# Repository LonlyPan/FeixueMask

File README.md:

# 飞雪面具控制板源码

- **[English](/README_EN.md)**

飞雪面具控制板是[飞雪面具](https://www.bilibili.com/video/BV1Dy4y1i72c)的配套产品。

## 如何找到文件

### 00_Priority README
该目录下存放了该控制板项目的全部**技术文档**，对该项目的程序源码、PCB设计都有详细说明，请首先阅读。
>文档目前尚未编写完成
>
### 01_Firmware
该目录下存放了 **软件/程序** 相关的全部源文件

### 02_Electronics
该目录下存放了 **电路/PCB** 相关的全部源文件

### 04_others
即不属于 软件/程序 也不属于 电路/PCB，但和本项目相关的其它文件

###  README.txt
每个文件夹下都有该文档，请**首先阅读**。这包含有其所处文件夹的阅读索引及一些重要说明。

## FeixueMask 1.0
FeixueMask 1.0 是该固件的初始版本，已经经过测试，可正常使用。

在[发布页面](https://github.com/LonlyPan/FeixueMask/releases)下载早期版本的FeixueMask固件。
>目前还未发布任何历史版本

## 支持

为了获得最佳的配置和故障排除帮助，请使用以下资源：
- 哔哩哔哩：[猩造](https://space.bilibili.com/16614468/)  
- 聊天催更Q群：779627778

## 许可协议

FeixueMask 是遵循 [GPL license](/LICENSE) 协议发行的，因为我们相信开放式开发。 GPL附带了权利和义务。 无论您使用 FeixueMask 固件作为开源产品还是封闭源产品的驱动程序，都必须保持 FeixueMask 开放，并且必须根据要求向最终用户提供兼容的 FeixueMask 源代码。 遵守 FeixueMask 许可证的最直接方法是在 Github 上制作 FeixueMask 的分支，执行您的修改，并将用户引导到您修改后的分支。

虽然我们不能禁止在具有封闭源代码或有专利保护的产品中使用此代码，但我们还是希望您选择其他固件，或者最好自己制作。

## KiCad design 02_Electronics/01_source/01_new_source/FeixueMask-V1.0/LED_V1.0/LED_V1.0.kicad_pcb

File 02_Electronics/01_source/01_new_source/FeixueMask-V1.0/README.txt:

LED_V1.0 -------------------------------- LED灯板设计源文件
main_V1.0 ------------------------------- 主控板设计源文件
最终输出文件 ----------------------------- BOM、Gerber、原理图pdf

A1.0  2020-08-18
  原理图错误：
    1. Q1 引脚1、2颠倒（main、LED）
    2. RX接MCU引脚错误，应接PA10（main）
    3. 电容C2~5 值错误，应为 0.1uF（main）

V1.0  2020-08-21
   版本更新：
     1. 修复上一版设计错误（main、LED）
     2. LED灯板重新设计，三色灯改为单色灯（LED）
  版本错误：

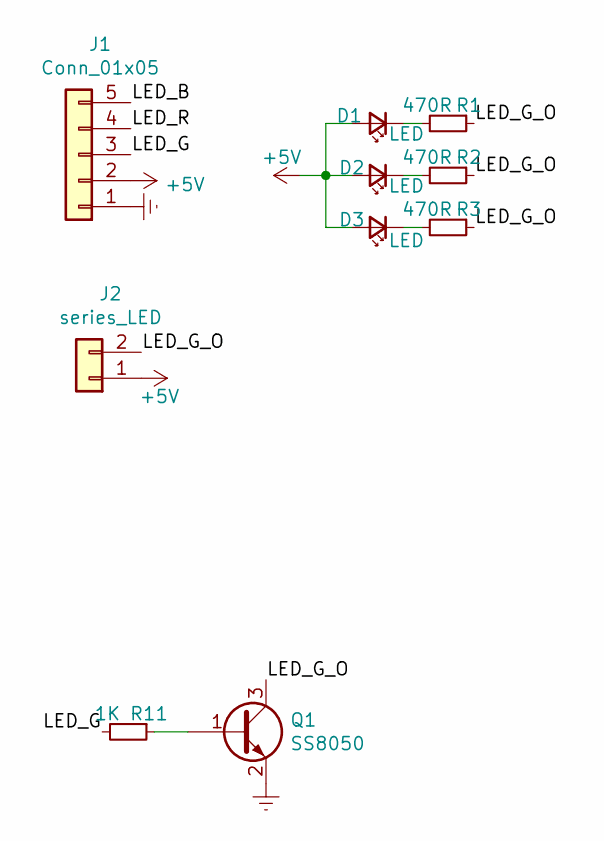
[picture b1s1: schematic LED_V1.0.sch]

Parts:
D1, D2, D3: LED; LED_0805_2012Metric
J1: Conn_01x05; FPC-0.7x5-Handsoldering
J2: series_LED; Pad-2.2mm_1.5x1.5
Q1: SS8050; SOT-23
R1, R2, R3: 470R; R_0603_1608Metric
R11: 1K; R_0603_1608Metric

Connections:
+5V: D1.2 (A), D2.2 (A), D3.2 (A), J1.2, J2.1
/LED_B: J1.5
/LED_G: J1.3, R11.2
/LED_G_O: J2.2, Q1.3 (C), R1.1, R2.1, R3.1
/LED_R: J1.4
Earth: J1.1, Q1.2 (E)
unnamed: D1.1 (K), R1.2
unnamed: D2.1 (K), R2.2
unnamed: D3.1 (K), R3.2
unnamed: Q1.1 (B), R11.1

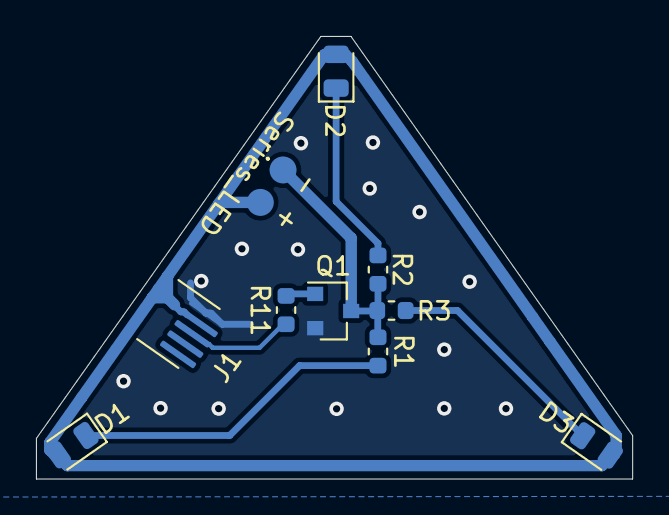
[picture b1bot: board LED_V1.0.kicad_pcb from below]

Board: 2 copper layers, 33.1 x 24.6 mm, 10 parts (10 on the bottom side), 8 nets.

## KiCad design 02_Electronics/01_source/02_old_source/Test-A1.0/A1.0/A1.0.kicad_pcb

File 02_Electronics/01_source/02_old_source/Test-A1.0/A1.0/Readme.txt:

R2 R3标注颠倒
STM32 RX引脚错误，PA8改为PA10

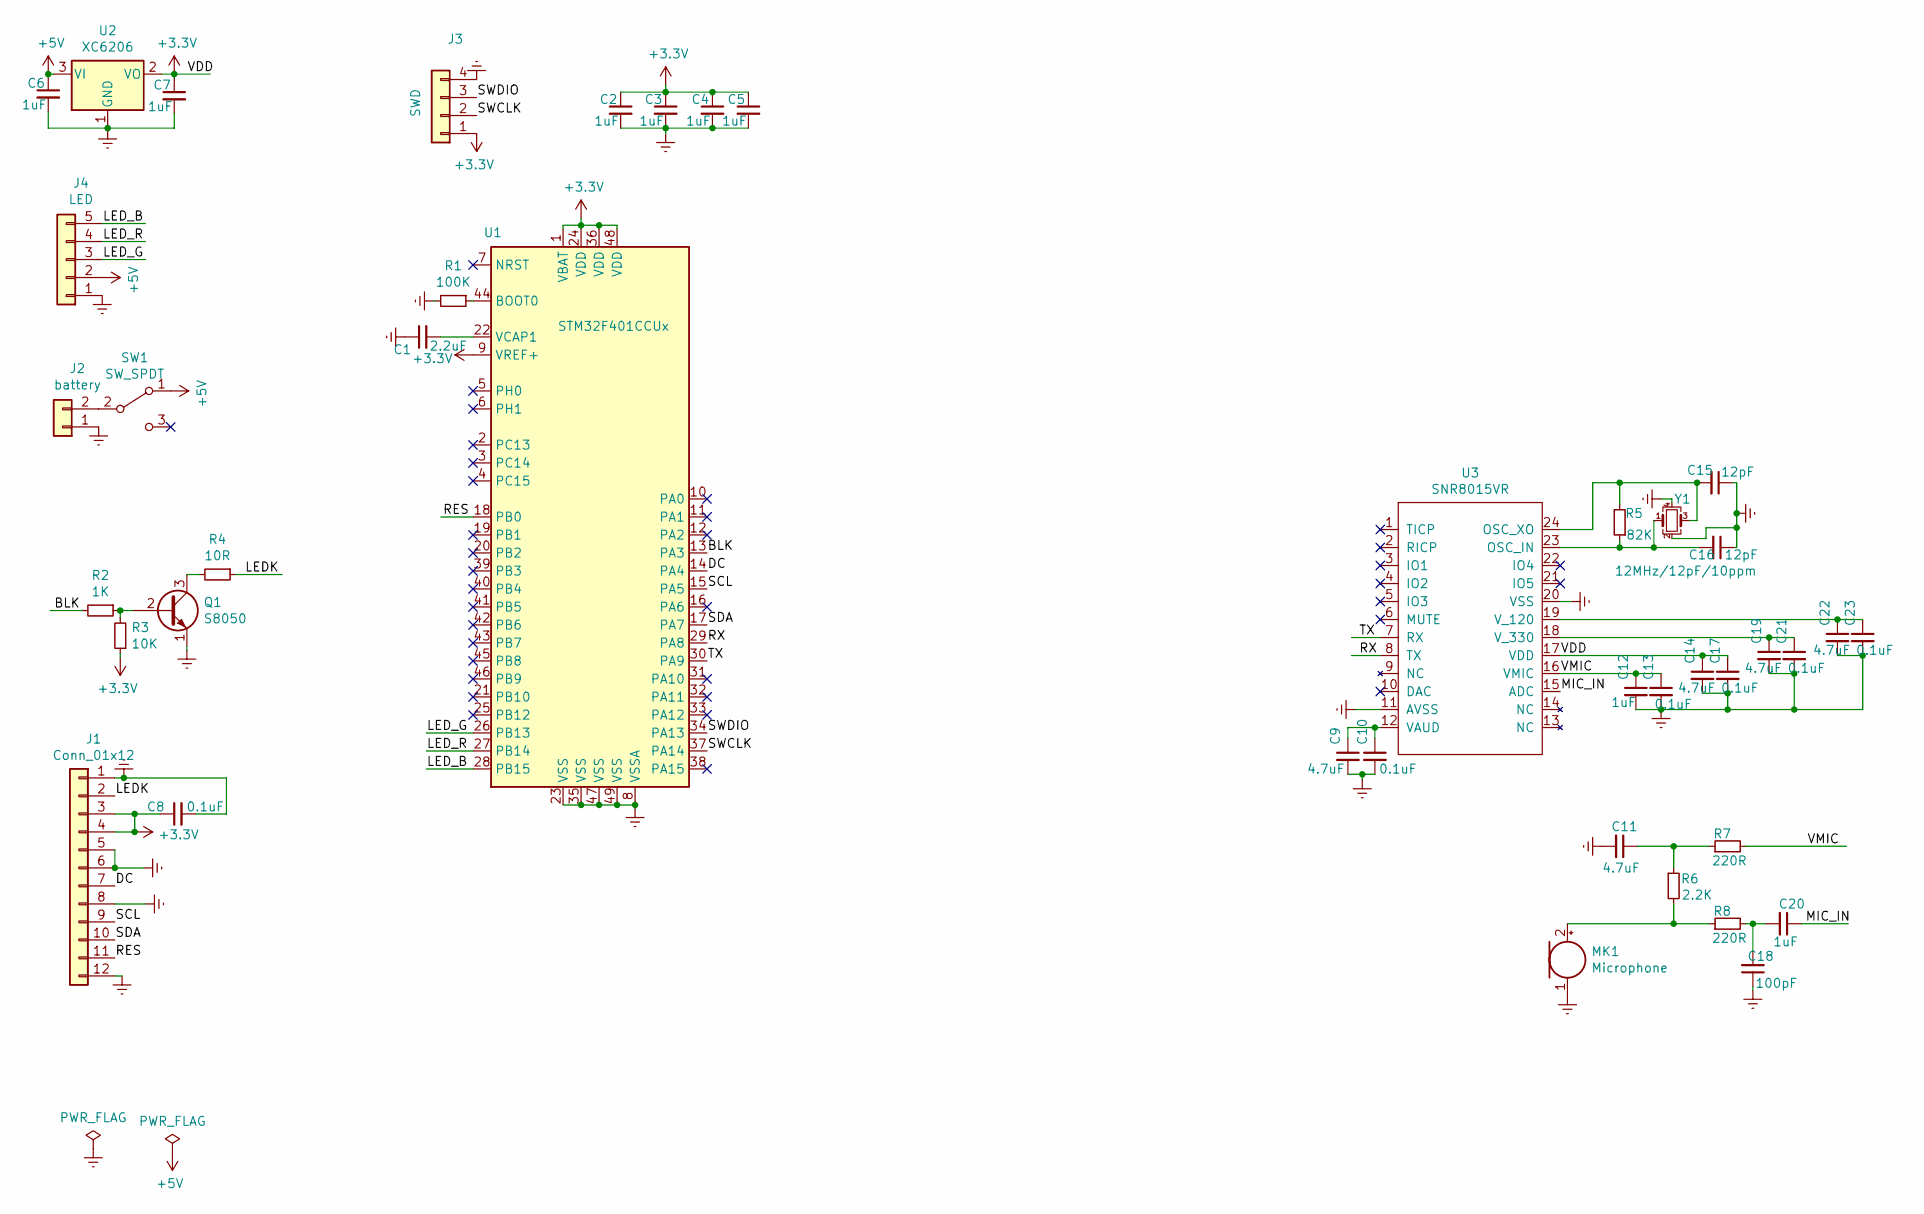
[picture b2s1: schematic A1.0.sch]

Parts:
C1: 2.2uF; C_0603_1608Metric
C2, C3, C4, C5, C6, C7, C12, C20: 1uF; C_0603_1608Metric
C8, C10, C13, C17, C21, C23: 0.1uF; C_0603_1608Metric
C9, C11, C14, C19, C22: 4.7uF; C_0603_1608Metric
C15, C16: 12pF; C_0603_1608Metric
C18: 100pF; C_0603_1608Metric
J1: Conn_01x12; FPC-0.7-Handsoldering-1.28-TFT
J2: battery; Speaker
J3: SWD; Con-1x4-P1.25mm
J4: LED; FPC-0.7x5-Handsoldering
MK1: Microphone; Condenser-Microphone-4012
Q1: S8050; SOT-23
R1: 100K; R_0603_1608Metric
R2: 1K; R_0603_1608Metric
R3: 10K; R_0603_1608Metric
R4: 10R; R_0603_1608Metric
R5: 82K; R_0603_1608Metric
R6: 2.2K; R_0603_1608Metric
R7, R8: 220R; R_0603_1608Metric
SW1: SW_SPDT; MSKT-12C00-switch-smd
U1: STM32F401CCUx; QFN-48-1EP_7x7mm_P0.5mm_EP5.6x5.6mm
U2: XC6206; SOT-23
U3: SNR8015VR; QSOP-24_3.9x8.7mm_P0.635mm
Y1: 12MHz/12pF/10ppm; Crystal_SMD_2520-4Pin_2.5x2.0mm

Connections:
+3V3: C2.1, C3.1, C4.1, C5.1, C7.1, C8.1, C14.1, C17.1, J1.3, J1.4, J3.1, R3.1, U1.1 (VBAT), U1.9 (VREF+), U1.24 (VDD), U1.36 (VDD), U1.48 (VDD), U2.2 (VO), U3.17 (VDD)
+5V: C6.1, J4.2, SW1.1 (A), U2.3 (VI)
/BLK: R2.2, U1.13 (PA3)
/DC: J1.7, U1.14 (PA4)
/LEDK: J1.2, R4.1
/LED_B: J4.5, U1.28 (PB15)
/LED_G: J4.3, U1.26 (PB13)
/LED_R: J4.4, U1.27 (PB14)
/MIC_IN: C20.1, U3.15 (ADC)
/RES: J1.11, U1.18 (PB0)
/RX: U1.29 (PA8), U3.8 (TX)
/SCL: J1.9, U1.15 (PA5)
/SDA: J1.10, U1.17 (PA7)
/SWCLK: J3.2, U1.37 (PA14)
/SWDIO: J3.3, U1.34 (PA13)
/TX: U1.30 (PA9), U3.7 (RX)
/VMIC: C12.1, C13.1, R7.2, U3.16 (VMIC)
Earth: C1.1, C2.2, C3.2, C4.2, C5.2, C6.2, C7.2, C8.2, C9.2, C10.2, C11.2, C12.2, C13.2, C14.2, C15.1, C16.1, C17.2, C18.1, C19.2, C21.2, C22.2, C23.2, J1.1, J1.5, J1.6, J1.8, J1.12, J2.1, J3.4, J4.1, MK1.1 (-), Q1.1 (E), R1.2, U1.8 (VSSA), U1.23 (VSS), U1.35 (VSS), U1.47 (VSS), U1.49 (VSS), U2.1 (GND), U3.11 (AVSS), U3.20 (VSS), Y1.2, Y1.4
unnamed: C1.2, U1.22 (VCAP1)
unnamed: C9.1, C10.1, U3.12 (VAUD)
unnamed: C11.1, R6.1, R7.1
unnamed: C15.2, R5.2, U3.24 (OSC_XO), Y1.3
unnamed: C16.2, R5.1, U3.23 (OSC_IN), Y1.1
unnamed: C18.2, C20.2, R8.2
unnamed: C19.1, C21.1, U3.18 (V_330)
unnamed: C22.1, C23.1, U3.19 (V_120)
unnamed: J2.2, SW1.2 (B)
unnamed: MK1.2 (+), R6.2, R8.1
unnamed: Q1.2 (B), R2.1, R3.2
unnamed: Q1.3 (C), R4.2
unnamed: R1.1, U1.44 (BOOT0)

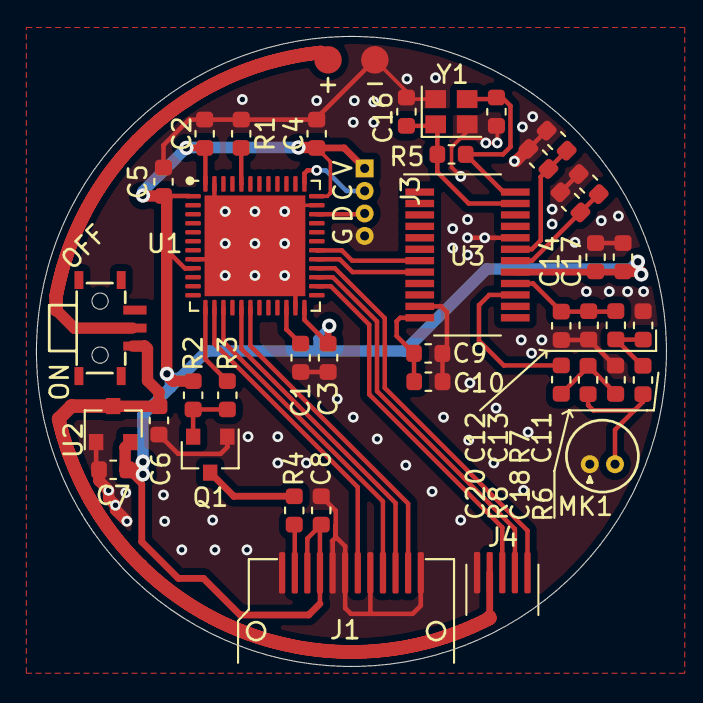
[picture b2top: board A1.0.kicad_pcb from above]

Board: 2 copper layers, 35.0 x 35.0 mm, 42 parts (0 on the bottom side), 31 nets.

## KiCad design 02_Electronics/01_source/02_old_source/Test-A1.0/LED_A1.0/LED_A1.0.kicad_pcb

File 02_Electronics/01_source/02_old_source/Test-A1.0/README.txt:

LED_A1.0 -------------------------------- LED灯板设计源文件
A1.0 ------------------------------- 主控板设计源文件

A1.0  2020-08-18
  原理图错误：
    1. Q1 引脚1、2颠倒（main、LED）
    2. RX接MCU引脚错误，应接PA10（main）
    3. 电容C2~5 值错误，应为 0.1uF（main）

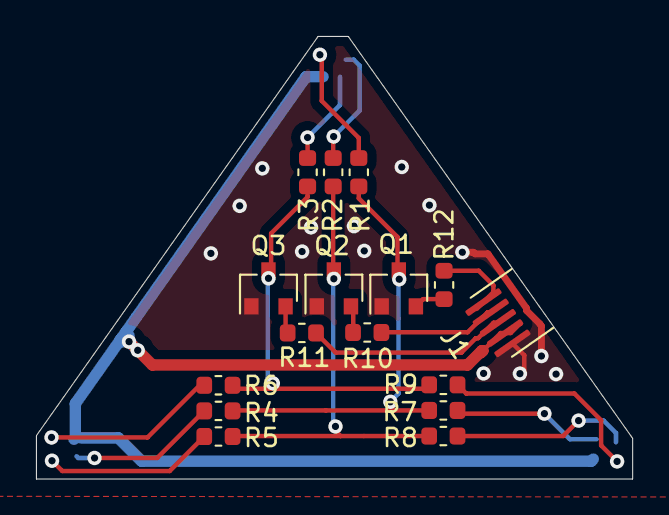
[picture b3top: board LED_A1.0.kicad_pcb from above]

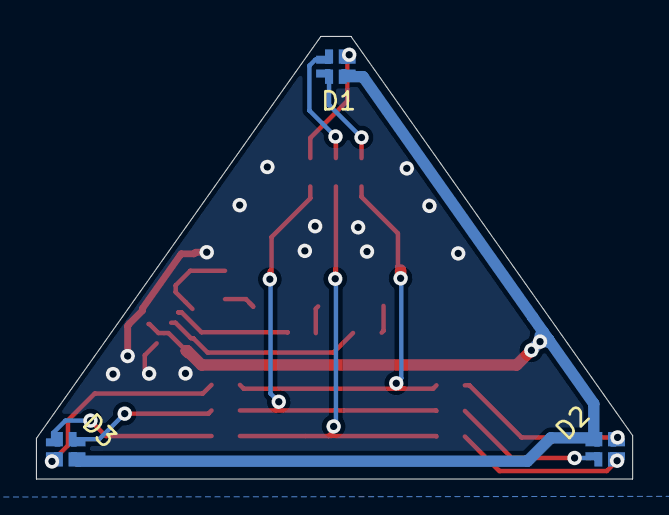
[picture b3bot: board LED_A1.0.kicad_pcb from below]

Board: 2 copper layers, 33.1 x 24.6 mm, 19 parts (3 on the bottom side), 20 nets.

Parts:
D1, D2, D3: LED_ARGB; RGD-compatible
J1: Conn_01x05; FPC-0.7x5-Handsoldering
Q1, Q2, Q3: S8050; SOT-23
R1, R2, R3, R4, R5, R6, R7, R8, R9: 10K; R_0603_1608Metric
R10, R11, R12: 1K; R_0603_1608Metric

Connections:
+5V: D1.1, D2.1, D3.1, J1.2
/LED_B: J1.5, R12.2
/LED_B_O: Q1.3, R1.1, R4.1, R7.1
/LED_G: J1.3, R11.2
/LED_G_O: Q3.3, R3.1, R6.1, R9.1
/LED_R: J1.4, R10.2
/LED_R_O: Q2.3, R2.1, R5.1, R8.1
Earth: J1.1, Q1.1, Q2.1, Q3.1
unnamed: D1.2, R3.2
unnamed: D1.3, R2.2
unnamed: D1.4, R1.2
unnamed: D2.2, R6.2
unnamed: D2.3, R5.2
unnamed: D2.4, R4.2
unnamed: D3.2, R9.2
unnamed: D3.3, R8.2
unnamed: D3.4, R7.2
unnamed: Q1.2, R12.1
unnamed: Q2.2, R10.1
unnamed: Q3.2, R11.1

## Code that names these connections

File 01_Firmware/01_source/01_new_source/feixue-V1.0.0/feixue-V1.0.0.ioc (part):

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Mcu.Name=STM32F401C(B-C)Ux
Mcu.Package=UFQFPN48
Mcu.UserName=STM32F401CCUx
PA10.Mode=Asynchronous
PA10.Signal=USART1_RX
PA13.Mode=Serial_Wire
PA13.Signal=SYS_JTMS-SWDIO
PA14.Mode=Serial_Wire
PA14.Signal=SYS_JTCK-SWCLK
PA3.GPIOParameters=GPIO_Speed,PinState,GPIO_PuPd,GPIO_Label
PA3.GPIO_Label=BLK
PA3.GPIO_PuPd=GPIO_PULLUP
PA3.GPIO_Speed=GPIO_SPEED_FREQ_HIGH
PA3.PinState=GPIO_PIN_SET
PA3.Signal=GPIO_Output
PA4.GPIOParameters=GPIO_Speed,PinState,GPIO_PuPd,GPIO_Label
PA4.GPIO_Label=DC
PA4.GPIO_PuPd=GPIO_PULLUP
PA4.GPIO_Speed=GPIO_SPEED_FREQ_HIGH
PA4.PinState=GPIO_PIN_SET
PA4.Signal=GPIO_Output
PA5.Mode=TX_Only_Simplex_Unidirect_Master
PA5.Signal=SPI1_SCK
PA7.Mode=TX_Only_Simplex_Unidirect_Master
PA7.Signal=SPI1_MOSI
PA9.Mode=Asynchronous
PA9.Signal=USART1_TX
PB0.GPIOParameters=GPIO_Speed,PinState,GPIO_PuPd,GPIO_Label
PB0.GPIO_Label=RES
PB0.GPIO_PuPd=GPIO_PULLUP
PB0.GPIO_Speed=GPIO_SPEED_FREQ_HIGH
PB0.PinState=GPIO_PIN_SET
PB0.Signal=GPIO_Output
PB13.GPIOParameters=GPIO_Speed,PinState,GPIO_PuPd,GPIO_Label
PB13.GPIO_Label=LED_G
PB13.GPIO_PuPd=GPIO_PULLUP
PB13.GPIO_Speed=GPIO_SPEED_FREQ_VERY_HIGH
PB13.PinState=GPIO_PIN_RESET
PB13.Signal=GPIO_Output
PB14.GPIOParameters=GPIO_Speed,PinState,GPIO_PuPd,GPIO_Label
PB14.GPIO_Label=LED_R
PB14.GPIO_PuPd=GPIO_PULLUP
PB14.GPIO_Speed=GPIO_SPEED_FREQ_VERY_HIGH
PB14.PinState=GPIO_PIN_RESET
PB14.Signal=GPIO_Output
PB15.GPIOParameters=GPIO_Speed,GPIO_PuPd,GPIO_Label
PB15.GPIO_Label=LED_B
PB15.GPIO_PuPd=GPIO_PULLUP
PB15.GPIO_Speed=GPIO_SPEED_FREQ_VERY_HIGH
PB15.Signal=GPIO_Output
RCC.HSE_VALUE=25000000
RCC.SYSCLKFreq_VALUE=84000000
RCC.SYSCLKSource=RCC_SYSCLKSOURCE_PLLCLK
board=custom

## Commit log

2020-12-21 test
2020-12-21 test1
2020-12-21 README updata
2020-12-23 updata
